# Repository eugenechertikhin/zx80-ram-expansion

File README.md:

# ZX80 ram expansion card

This expansion card use 2x23 edge connector

## This is redrawn scheema from internet

## Schema and pcb in pdf

* [Scheema](images/zx80-ram-expansion-scheema.pdf)
* [PCB layout](images/zx80-ram-expansion-pcb.pdf)

## 3D renders

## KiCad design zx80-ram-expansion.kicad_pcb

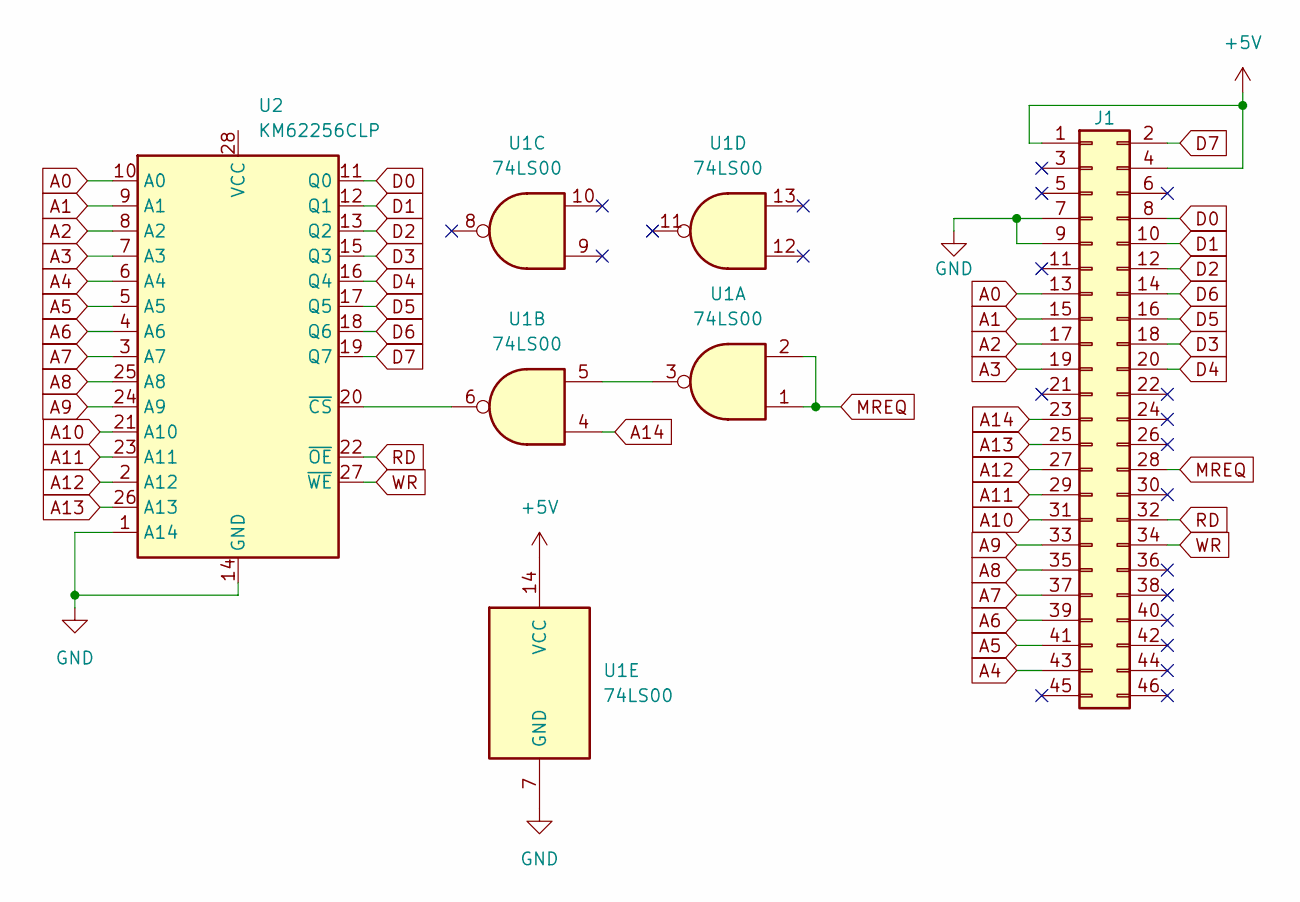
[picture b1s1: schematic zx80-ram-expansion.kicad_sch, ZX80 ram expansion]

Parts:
J1: Conn_02x23_Odd_Even; PinHeader_2x23_P2.54mm_Vertical
U1: 74LS00; DIP-14_W7.62mm_LongPads
U2: KM62256CLP; DIP-28_W15.24mm

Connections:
+5V: J1.1, J1.4, U1.14 (VCC)
A0: J1.13, U2.10 (A0)
A1: J1.15, U2.9 (A1)
A2: J1.17, U2.8 (A2)
A3: J1.19, U2.7 (A3)
A4: J1.43, U2.6 (A4)
A5: J1.41, U2.5 (A5)
A6: J1.39, U2.4 (A6)
A7: J1.37, U2.3 (A7)
A8: J1.35, U2.25 (A8)
A9: J1.33, U2.24 (A9)
A10: J1.31, U2.21 (A10)
A11: J1.29, U2.23 (A11)
A12: J1.27, U2.2 (A12)
A13: J1.25, U2.26 (A13)
A14: J1.23, U1.4
D0: J1.8, U2.11 (Q0)
D1: J1.10, U2.12 (Q1)
D2: J1.12, U2.13 (Q2)
D3: J1.18, U2.15 (Q3)
D4: J1.20, U2.16 (Q4)
D5: J1.16, U2.17 (Q5)
D6: J1.14, U2.18 (Q6)
D7: J1.2, U2.19 (Q7)
GND: J1.7, J1.9, U1.7 (GND), U2.1 (A14), U2.14 (GND)
MREQ: J1.28, U1.1, U1.2
unnamed: U1.3, U1.5
unnamed: U1.6, U2.20 (~CS)
RD: J1.32, U2.22 (~OE)
WR: J1.34, U2.27 (~WE)

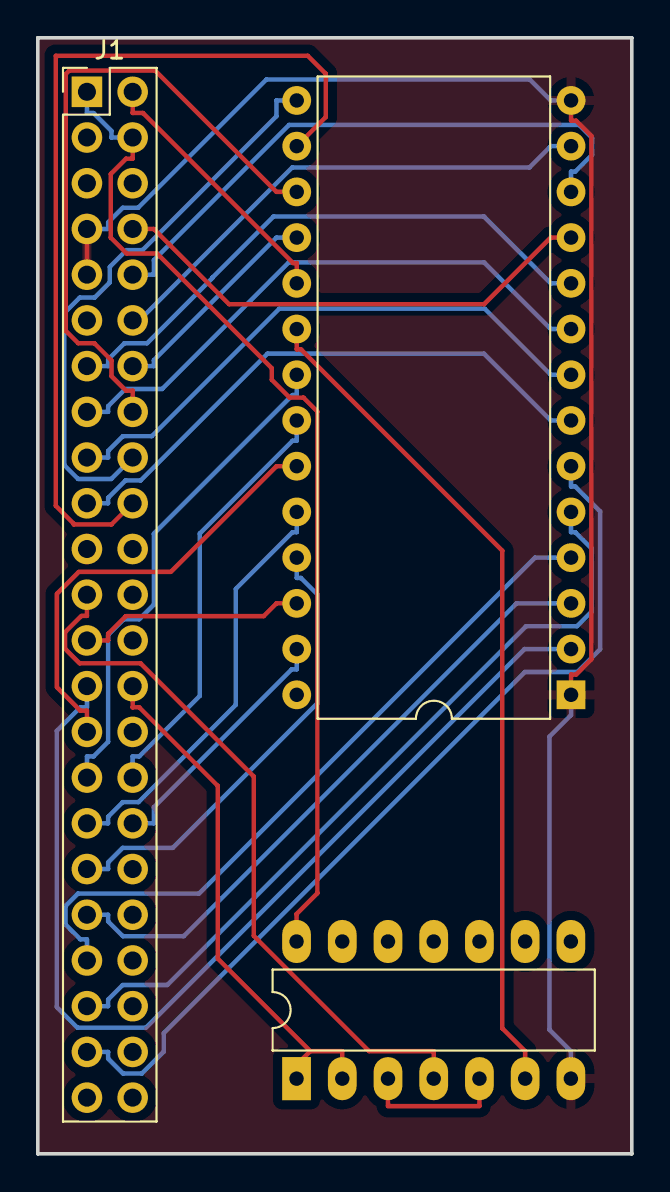
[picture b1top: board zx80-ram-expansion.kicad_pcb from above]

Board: 2 copper layers, 33.0 x 62.0 mm, 3 parts (0 on the bottom side), 30 nets.

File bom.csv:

"Id";"Designator";"Footprint";"Quantity";"Designation";"Supplier and ref";
1;"U2";"DIP-28_W15.24mm";1;"KM62256CLP";;;
2;"U1";"DIP-14_W7.62mm_LongPads";1;"74LS00";;;
3;"J1";"PinHeader_2x23_P2.54mm_Vertical";1;"Conn_02x23_Odd_Even";;;

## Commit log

2023-12-18 initial
2023-12-18 add schemas
2023-12-18 add 3d renders
2024-09-04 small correction, remove via hole
